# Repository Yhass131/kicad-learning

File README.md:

# KiCad-learning

Working through KiCad from scratch — datasheet reading, custom symbols, custom footprints, and full board layouts, from schematic capture through fabrication files. Following [Steppe School's KiCad tutorial playlist](https://www.youtube.com/playlist?list=PLmXXQ1iFwiyK4I1KeTiDFBSFvOB2ja55Y).

This repo is a public log of my progress: every component library, footprint, and board I build while learning, along with notes on what each step actually taught me.

---

## Goals

- Get fluent enough in KiCad to design and route a real board end to end
- Build the habit of reading datasheets properly instead of trusting stock libraries
- Maintain my own symbol and footprint libraries I can reuse on future projects
- Document the process well enough that it doubles as portfolio work

---

## Repo Structure

```
kicad-learning/
├── libraries/
│   ├── symbols/           # Custom .kicad_sym files
│   └── footprints/        # Custom .pretty footprint libraries
├── projects/
│   └── led-driver/        # Full board: schematic, PCB, fabrication files
│       └── fabrication/   # Gerbers + BOM submitted to PCBWay
├── datasheets/            # Reference datasheets for parts used
└── images/                # Screenshots used in this README
```

---

## Work Log

### Videos 1–4 — Datasheet, Symbol, Footprint, LED Driver

**Part:** `CAT4104VP2` — `GT3` (LED driver)

**Datasheet review.** Pulled the pin assignments, absolute maximum ratings, and the recommended land pattern out of the datasheet.

**Footprint parameters:**

- Pad count:   `8`
- Row count:   `2`
- Pad pitch:   `0.50 mm`
- Pad width:   `0.30 mm`
- Pad length:  `0.68 mm`
- Row spacing: `2.72 mm`

Row spacing isn't given directly — it's the center-to-center distance between opposite pads, so I derived it from the overall land pattern width minus one pad length.

**Symbol.** Built the schematic symbol in the Symbol Editor with pin numbers, pin names, and electrical types set to match the datasheet.

*Schematic symbol for `CAT4104VP2`.*

**Footprint.** Built the matching footprint in the Footprint Editor using the recommended land pattern — pads, silkscreen outline, courtyard, and pin 1 marker.

*Footprint for `CAT4104VP2` (`GT3`).*

*3D preview with the model assigned.*

---

### Videos 5–6 — LEDs & USB Connector

**Part:** `10164359-00011LF` (USB connector)

This component acts as the board's power source.

**Datasheet review.**

Similar approach to the LED driver for the square pads, but the oval pads are different — they're plated through-holes, used for parts that need a mechanical anchor through the board. In this case, the USB plug is secured to the board through those four holes.

**Symbol for USB connector `10164359-00011LF`**

**Footprint.**

**3D preview**

**Part:** `158301265A` (LED)

**Datasheet review.**

Same approach as before for the square pads.

**Symbol for LED `158301265A`**

**Footprint.**

**3D preview**

---

### Video 7 — Schematic Capture & ERC

This schematic connects all the components to achieve a single goal: the LED driver keeps the LEDs lit, and both the driver and the LEDs are powered by the USB connector section. The `+5V_USB` tags are net labels — any tags sharing the same name are treated as electrically connected, removing the need for wires spanning across the schematic or between sections.

After finishing the design, the Electrical Rules Checker (ERC) was used to validate the schematic. Most issues found in this simple project were solved with minor adjustments in the Symbol Editor.

**What I learned:**

- Datasheets give you much more than pins: absolute maximum ratings, operating conditions, mechanical drawings, recommended land patterns, and thermal data all shape the design.
- Rolling your own symbols beats downloading them. Online libraries often break convention or contain errors you won't catch until fab.

---

### Video 8 and 9 — PCB Stackup, Routing & Filled Zones

*Top-level board footprint.*

Before routing, set up the board's physical stackup in Board Setup — layer count, dielectric and copper layer thicknesses, and copper weight — so trace-width/impedance calculations and DRC behave correctly downstream. With the stackup defined, routed the traces, set trace widths, and added filled copper zones (ground/power pours) with proper net assignment, following best-practice pour clearance and stitching.

---

### Video 10 — ERC Cleanup

Ran the ERC again and traced each error and warning back to its source — sometimes in the top-level schematic, sometimes in an individual component's schematic symbol or footprint. Kept checking and fixing until everything cleared, then cleaned up the silkscreen.

---

### Video 11 and 12 — Gerbers, BOM & PCBWay Submission

To send the design out for fabrication with PCBWay, I needed the Gerber files and a bill of materials (BOM). Gerbers were straightforward to export from the PCB editor. The BOM took more work — I had to reformat it in the Schematic Editor to match [PCBWay's expected format](https://www.pcbway.com/blog/PCB_Assembly/How_to_Build_a_BOM__Bill_Of_Materials_.html). Downloaded both into a manufacturing folder and uploaded them to PCBWay for review.

---

## Using These Libraries

To use the custom libraries in your own KiCad project:

1. **Preferences → Manage Symbol Libraries → Add** and point to `libraries/symbols/`
2. **Preferences → Manage Footprint Libraries → Add** and point to `libraries/footprints/`

---

## Tools

- **KiCad** `9.0`
- OS: `Windows 11`

---

## References

- Steppe School KiCad tutorial playlist — https://www.youtube.com/playlist?list=PLmXXQ1iFwiyK4I1KeTiDFBSFvOB2ja55Y
- KiCad official documentation — https://docs.kicad.org

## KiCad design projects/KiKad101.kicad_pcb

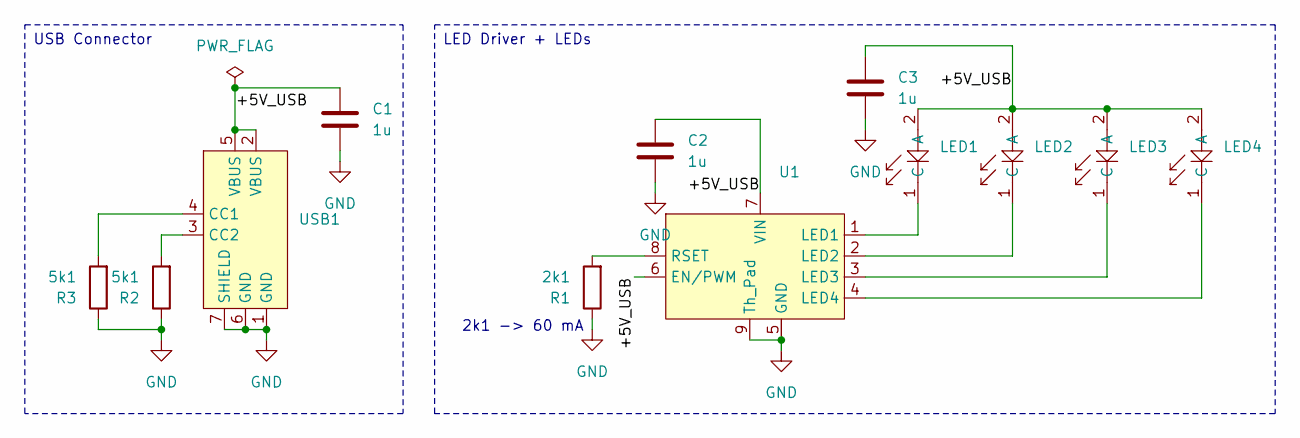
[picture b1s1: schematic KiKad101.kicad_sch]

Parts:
C1, C2, C3: 1u; C_0603_1608Metric; Part Number GMC04X7R105K10NT
LED1, LED2, LED3, LED4: 158301265A; Part Number 158301265A
R1: 2k1; R_0603_1608Metric; Part Number RMCF0603FT2K10
R2, R3: 5k1; R_0603_1608Metric; Part Number ERJ-3EKF5101V
U1: SOIC-8; Part Number CAT4104VP2-GT3
USB1: 10164359-00011LF; Part Number 10164359-00011LF

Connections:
/+5V_USB: C1.1, C2.1, C3.1, LED1.2 (A), LED2.2 (A), LED3.2 (A), LED4.2 (A), U1.6 (EN/PWM), U1.7 (VIN), USB1.2 (VBUS), USB1.5 (VBUS)
GND: C1.2, C2.2, C3.2, R1.1, R2.1, R3.1, U1.5 (GND), U1.9 (Th_Pad), USB1.1 (GND), USB1.6 (GND), USB1.7 (SHIELD)
unnamed: LED1.1 (C), U1.1 (LED1)
unnamed: LED2.1 (C), U1.2 (LED2)
unnamed: LED3.1 (C), U1.3 (LED3)
unnamed: LED4.1 (C), U1.4 (LED4)
unnamed: R2.2, USB1.3 (CC2)
unnamed: R3.2, USB1.4 (CC1)
unnamed: R1.2, U1.8 (RSET)

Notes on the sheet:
2k1 -> 60 mA
LED Driver + LEDs
USB Connector

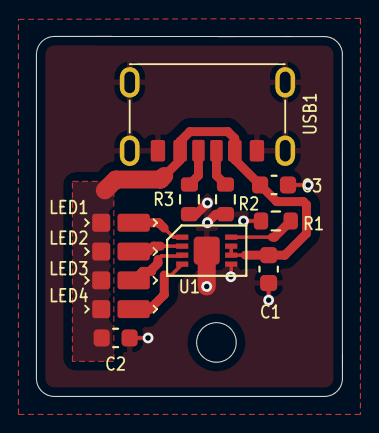
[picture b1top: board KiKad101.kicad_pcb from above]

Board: 2 copper layers, 17.0 x 20.0 mm, 12 parts (0 on the bottom side), 9 nets.

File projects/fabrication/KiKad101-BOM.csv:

"#","Reference","Qty","Manufacturer","Value","Part Number","Description"
"1","LED1,LED2,LED3,LED4","4","Würth Elektronik","~","158301265A","WL-SWTP SMT WHITE LED TOP VIEW P"
"2","USB1","1","Amphenol ICC (FCI)","~","10164359-00011LF","USB TYPE C RECEPTACLE RIGHT ANGL"
"3","U1","1","onsemi","~","CAT4104VP2-GT3","Constant Current LED Driver"
"4","R2,R3","2","Panasonic Industry","5k1","ERJ-3EKF5101V","RES SMD 5.1K OHM 1% 1/10W 0603"
"5","C1,C2,C3","3","Cal-Chip Electronics, Inc.","1u","GMC04X7R105K10NT","CAP0402 X7R 1UF 10% 10V"
"6","R1","1","Stackpole Electronics Inc","2k1","RMCF0603FT2K10","RES 2.1K OHM 1% 1/10W 0603"
